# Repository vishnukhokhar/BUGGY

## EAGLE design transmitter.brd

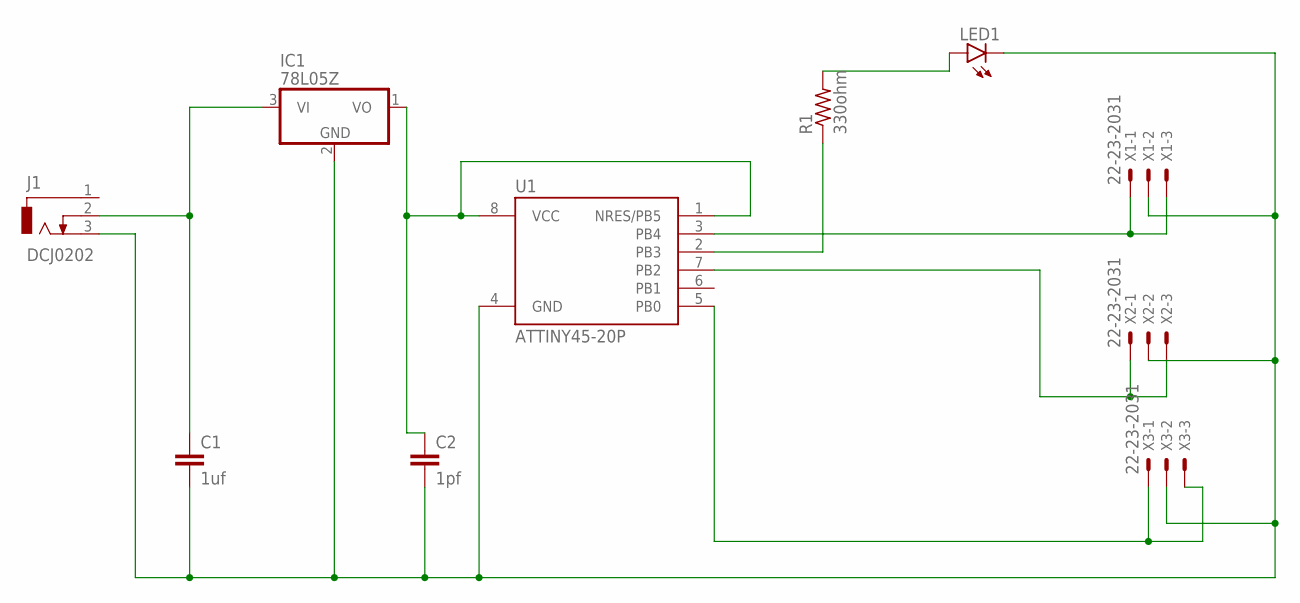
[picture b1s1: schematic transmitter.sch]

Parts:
C1: 1uf; C2.5-2
C2: 1pf; C2.5-2
IC1: 78L05Z; TO92
J1: DCJ0202
LED1: LED3MM
R1: 330ohm; 0207/10
U1: ATTINY45-20P; PDIP08_300MIL
X1, X2, X3: 22-23-2031

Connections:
unnamed: C1.1, IC1.3 (VI), J1.2
unnamed: C1.2, C2.2, IC1.2 (GND), J1.3, LED1.K (C), U1.4 (GND), X1.2, X2.2, X3.2
unnamed: C2.1, IC1.1 (VO), U1.1 (NRES/PB5), U1.8 (VCC)
unnamed: U1.5 (PB0), X3.1, X3.3
unnamed: LED1.A, R1.2
unnamed: U1.3 (PB4), X1.1, X1.3
unnamed: U1.7 (PB2), X2.1, X2.3
unnamed: R1.1, U1.2 (PB3)

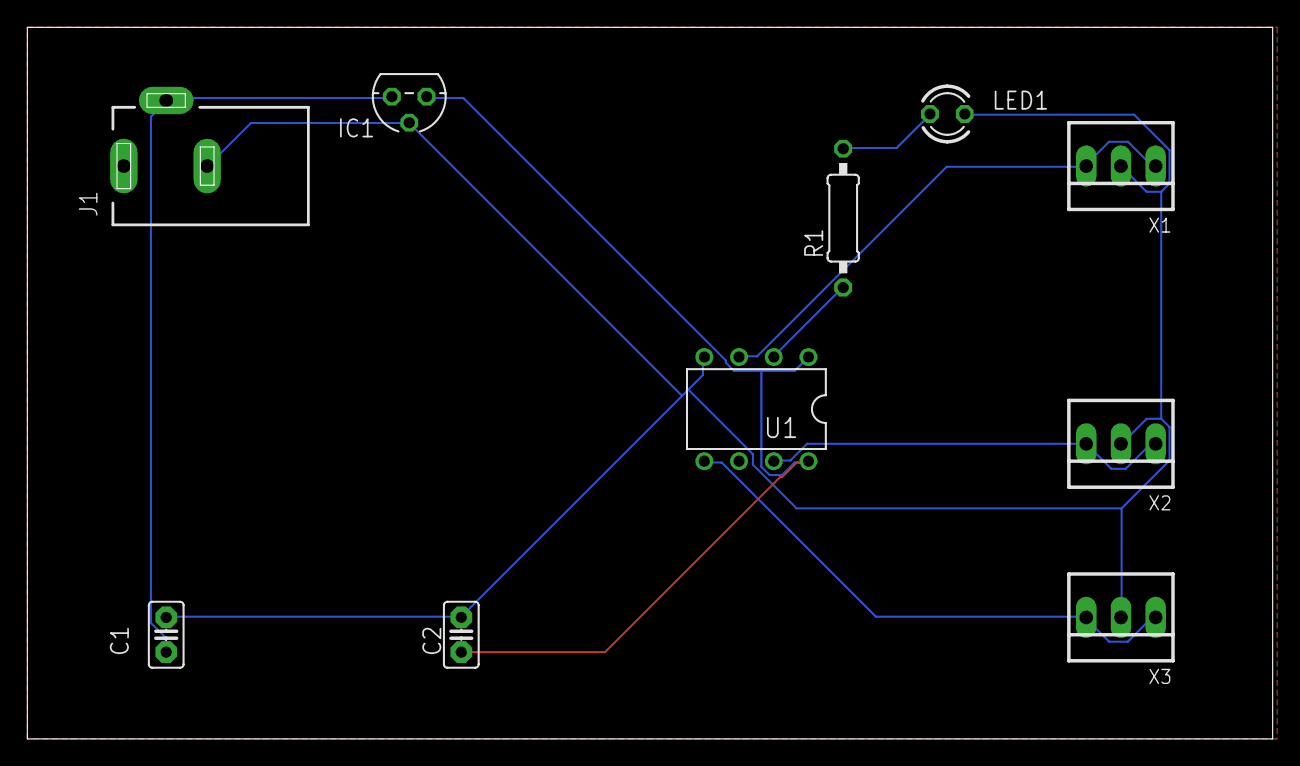
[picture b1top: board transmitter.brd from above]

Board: 2 copper layers, 91.1 x 52.1 mm, 10 parts (0 on the bottom side), 8 nets.

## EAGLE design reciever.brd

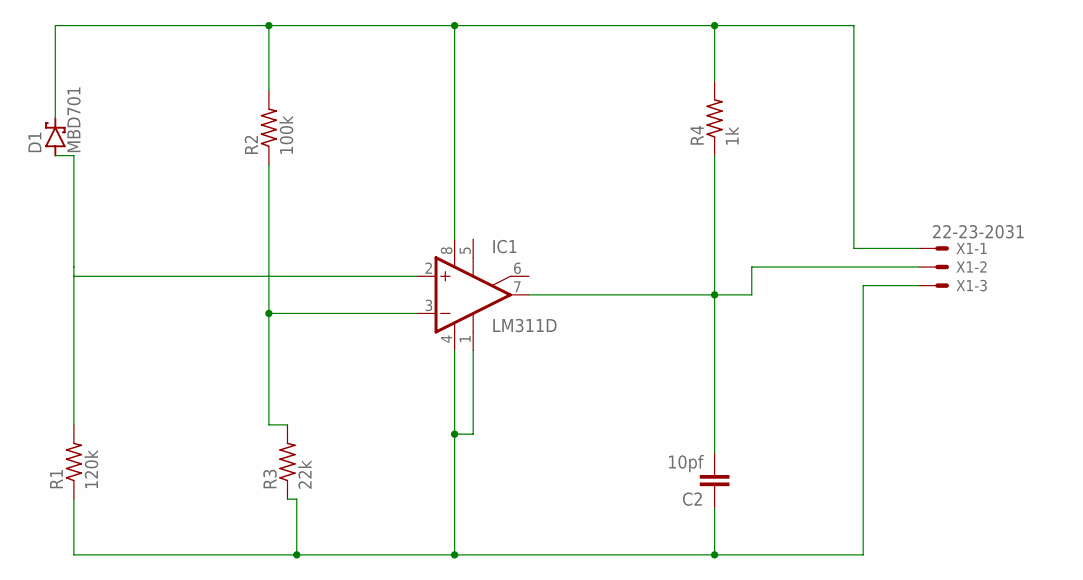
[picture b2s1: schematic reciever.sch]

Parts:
C2: 10pf; C2.5-2
D1: MBD701; TO92H
IC1: LM311D; SO08
R1: 120k; 0207/10
R2: 100k; 0207/10
R3: 22k; 0207/10
R4: 1k; 0207/10
X1: 22-23-2031

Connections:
unnamed: D1.2 (C), IC1.8 (V+), R2.2, R4.2, X1.1
unnamed: C2.1, IC1.1 (GND), IC1.4 (V-), R1.1, R3.1, X1.3
unnamed: D1.1 (A), IC1.2 (+IN), R1.2
unnamed: IC1.3 (-IN), R2.1, R3.2
unnamed: C2.2, IC1.7 (OUT), R4.1, X1.2

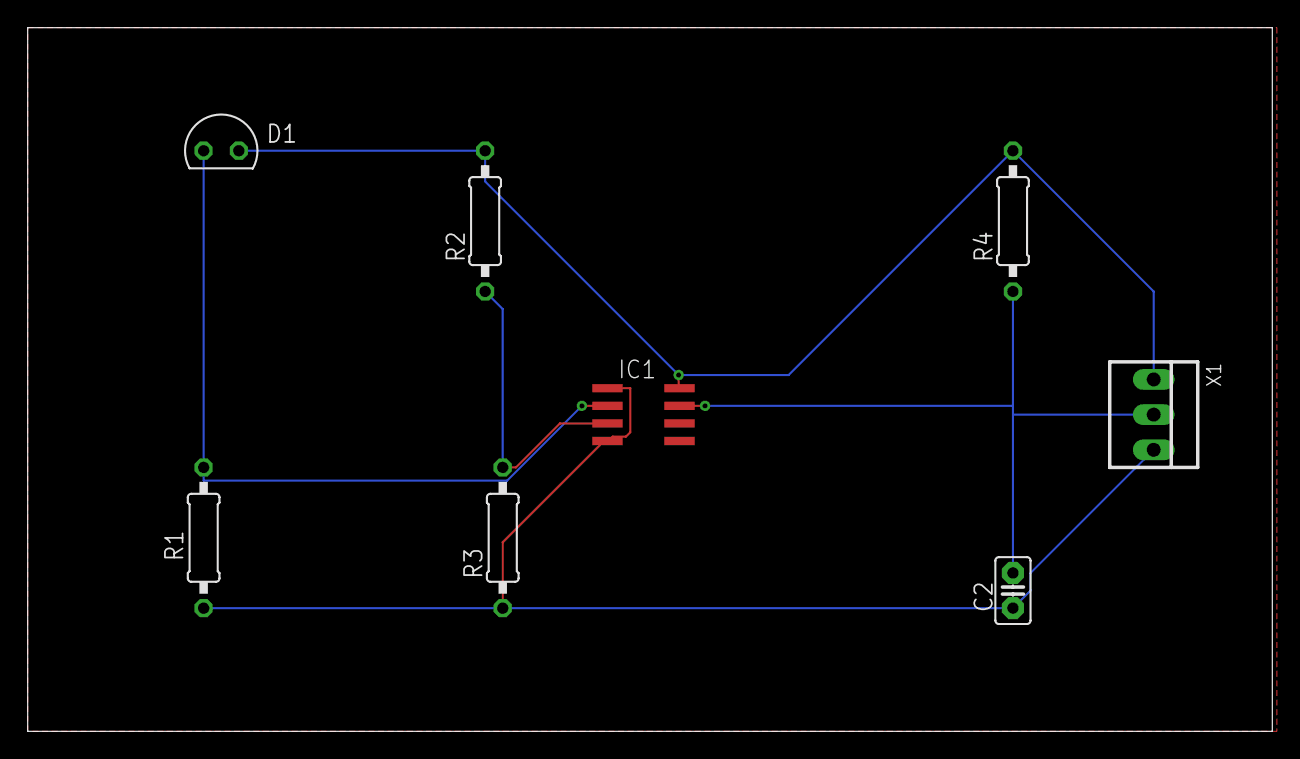
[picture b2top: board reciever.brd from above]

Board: 2 copper layers, 89.8 x 50.8 mm, 8 parts (0 on the bottom side), 5 nets.

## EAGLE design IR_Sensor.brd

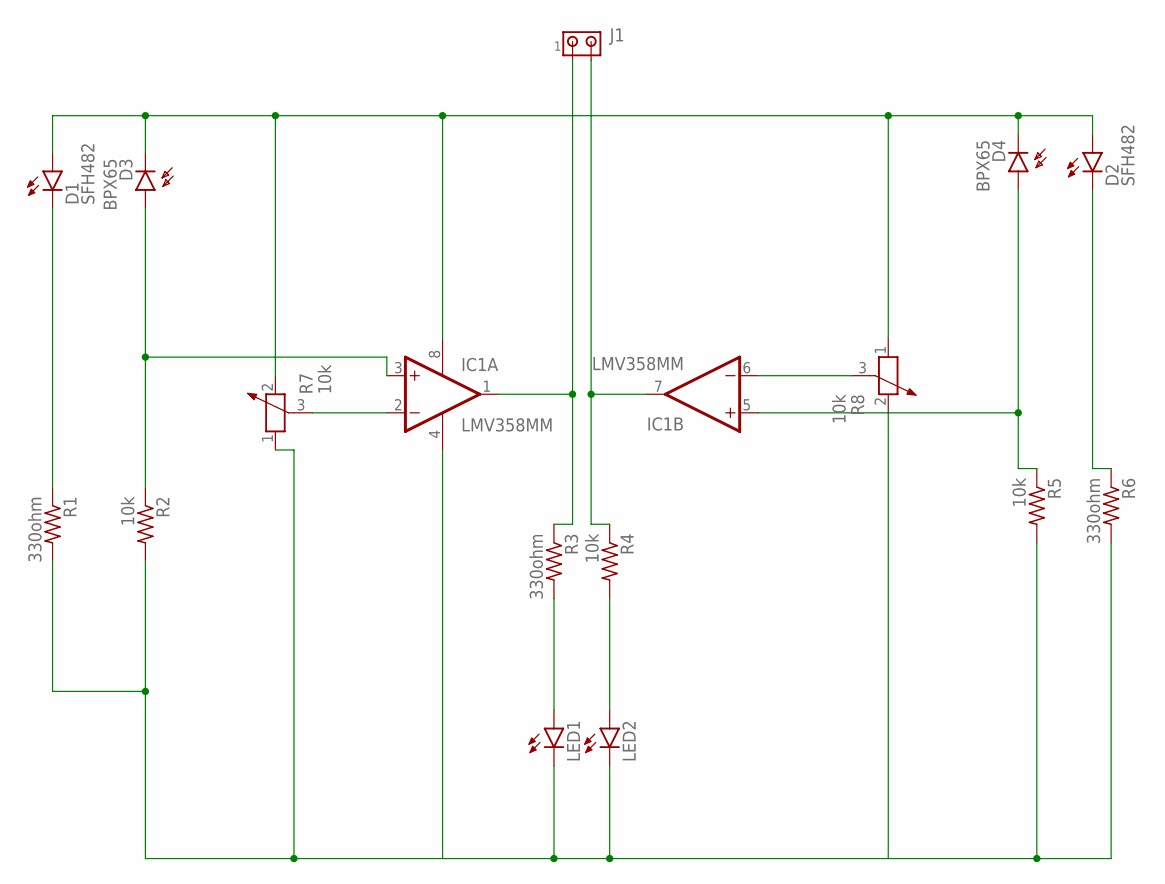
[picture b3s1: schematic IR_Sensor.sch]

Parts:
D1, D2: SFH482
D3, D4: BPX65
IC1: LMV358MM; MSOP08
J1: MTA02-100; 10X02MTA
LED1, LED2: LED3MM
R1, R3, R6: 330ohm; 0207/10
R2, R4, R5: 10k; 0207/10
R7, R8: 10k; PT-10

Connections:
unnamed: D1.A, D2.A, D3.K (C), D4.K (C), IC1.8 (V+), R7.2, R8.1
unnamed: IC1.4 (V-), LED1.K (C), LED2.K (C), R1.2, R2.2, R5.2, R6.2, R7.1, R8.2
unnamed: LED1.A, R3.2
unnamed: LED2.A, R4.2
unnamed: IC1.1 (OUT), J1.1, R3.1
unnamed: IC1.7 (OUT), J1.2, R4.1
unnamed: IC1.6 (-IN), R8.3
unnamed: D1.K (C), R1.1
unnamed: D3.A, IC1.3 (+IN), R2.1
unnamed: D4.A, IC1.5 (+IN), R5.1
unnamed: D2.K (C), R6.1
unnamed: IC1.2 (-IN), R7.3

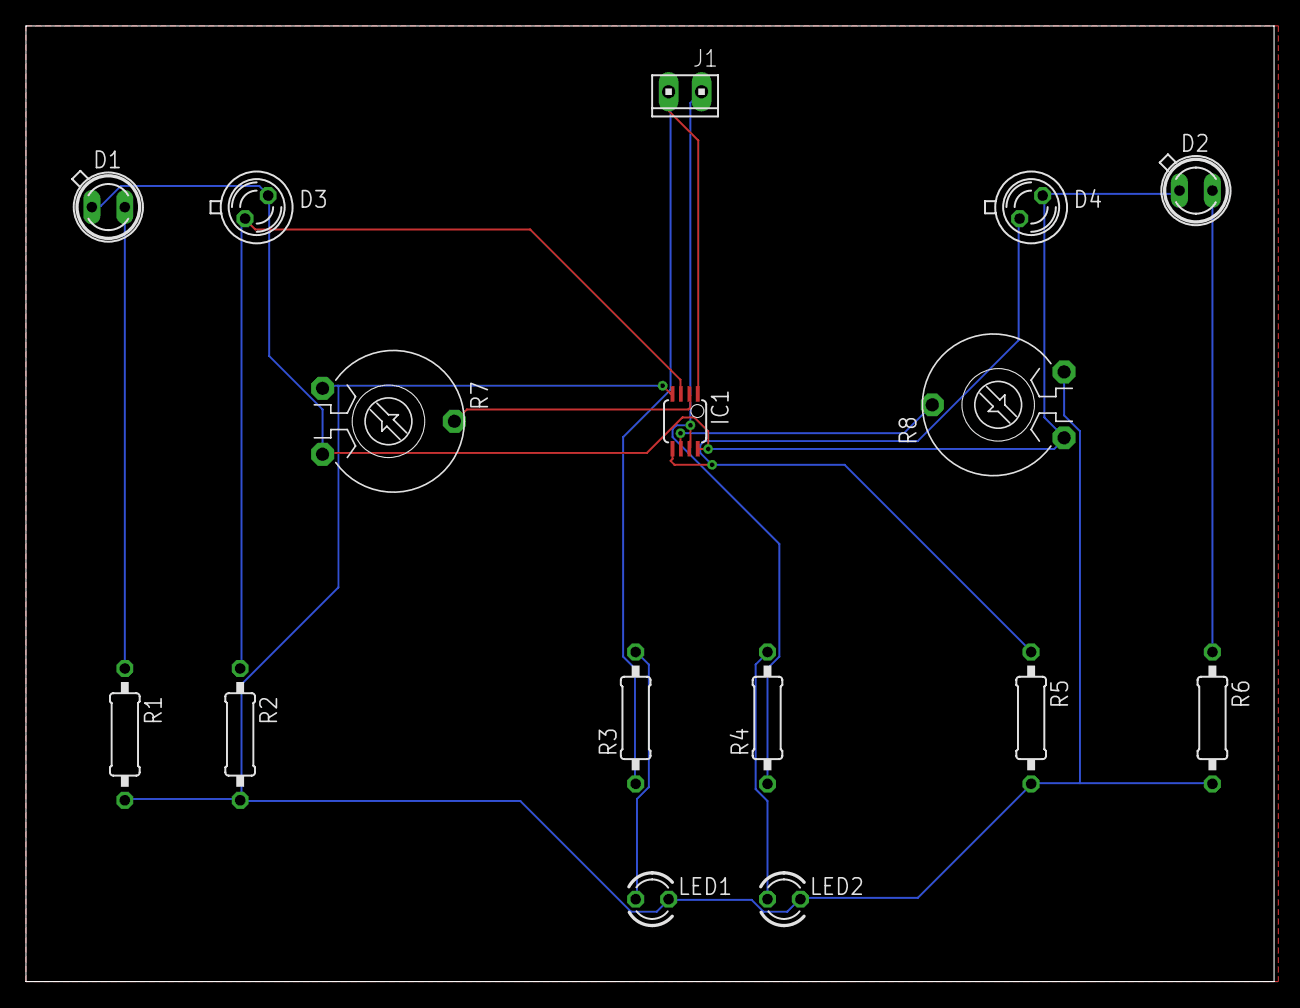
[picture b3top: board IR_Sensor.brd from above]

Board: 2 copper layers, 96.2 x 73.7 mm, 16 parts (0 on the bottom side), 12 nets.
